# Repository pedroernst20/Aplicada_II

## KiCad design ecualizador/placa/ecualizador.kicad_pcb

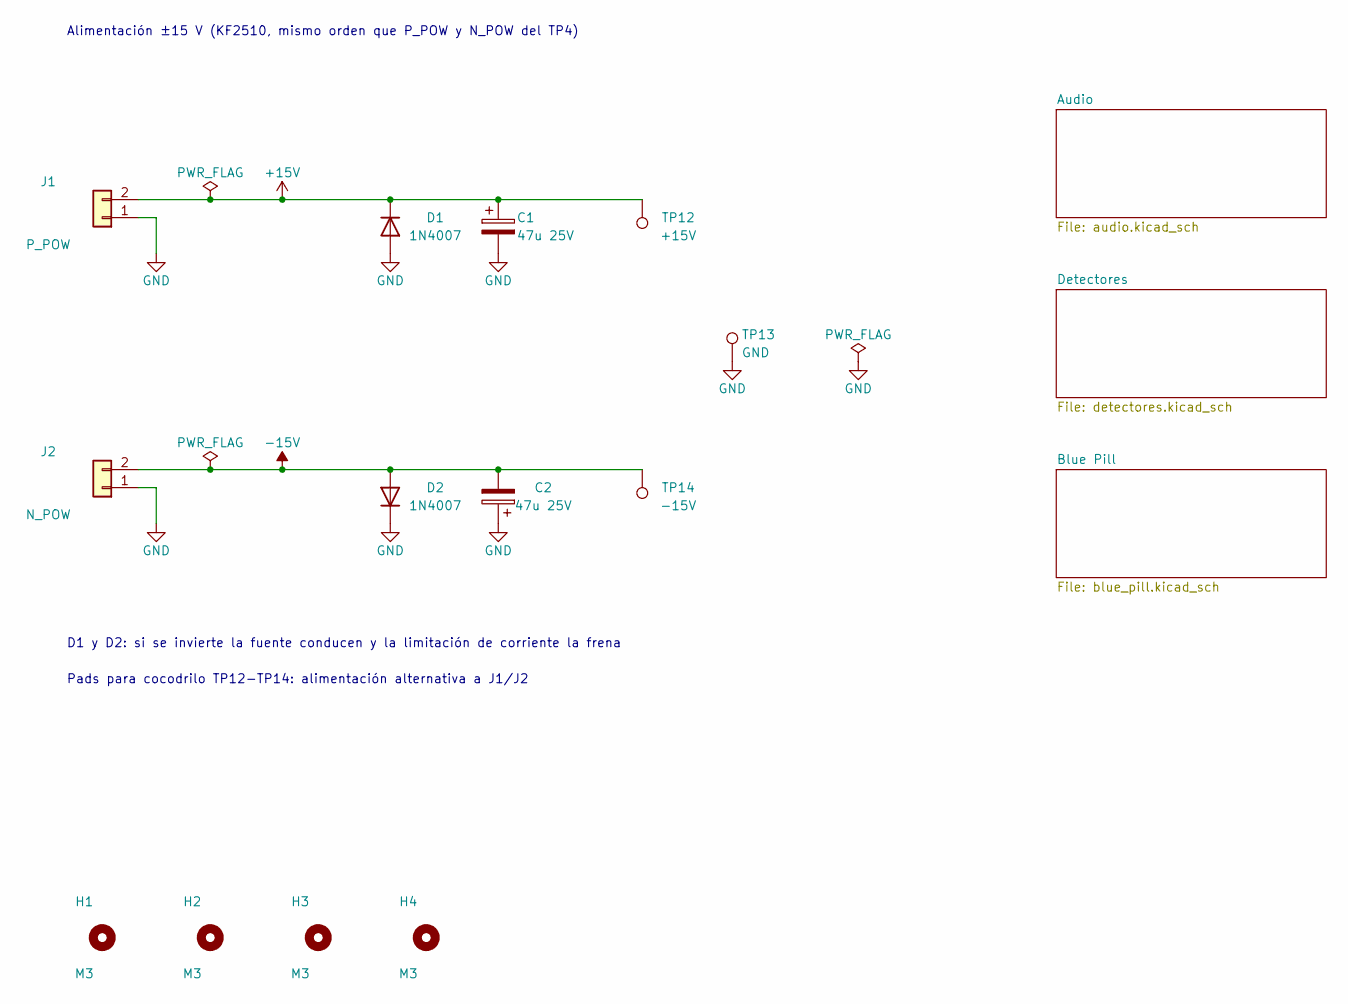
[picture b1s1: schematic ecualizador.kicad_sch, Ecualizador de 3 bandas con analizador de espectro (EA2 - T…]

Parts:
C1, C2: 47u 25V; CP_Radial_D6.3mm_P2.50mm
D1, D2: 1N4007; D_DO-41_SOD81_P10.16mm_Horizontal
H1, H2, H3, H4: M3; MountingHole_3.2mm_M3
J1: P_POW; KF2510_1x02_P2.54mm_Vertical
J2: N_POW; KF2510_1x02_P2.54mm_Vertical
TP12: +15V; Pad_Cocodrilo_6x8mm
TP13: GND; Pad_Cocodrilo_6x8mm
TP14: -15V; Pad_Cocodrilo_6x8mm

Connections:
+15V: C1.1, D1.1 (K), J1.2, TP12.1; also elsewhere on the board
-15V: C2.2, D2.2 (A), J2.2, TP14.1; also elsewhere on the board
GND: C1.2, C2.1, D1.2 (A), D2.1 (K), J1.1, J2.1, TP13.1; also elsewhere on the board

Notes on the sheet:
Alimentación ±15 V (KF2510, mismo orden que P_POW y N_POW del TP4)
D1 y D2: si se invierte la fuente conducen y la limitación de corriente la frena
Pads para cocodrilo TP12-TP14: alimentación alternativa a J1/J2

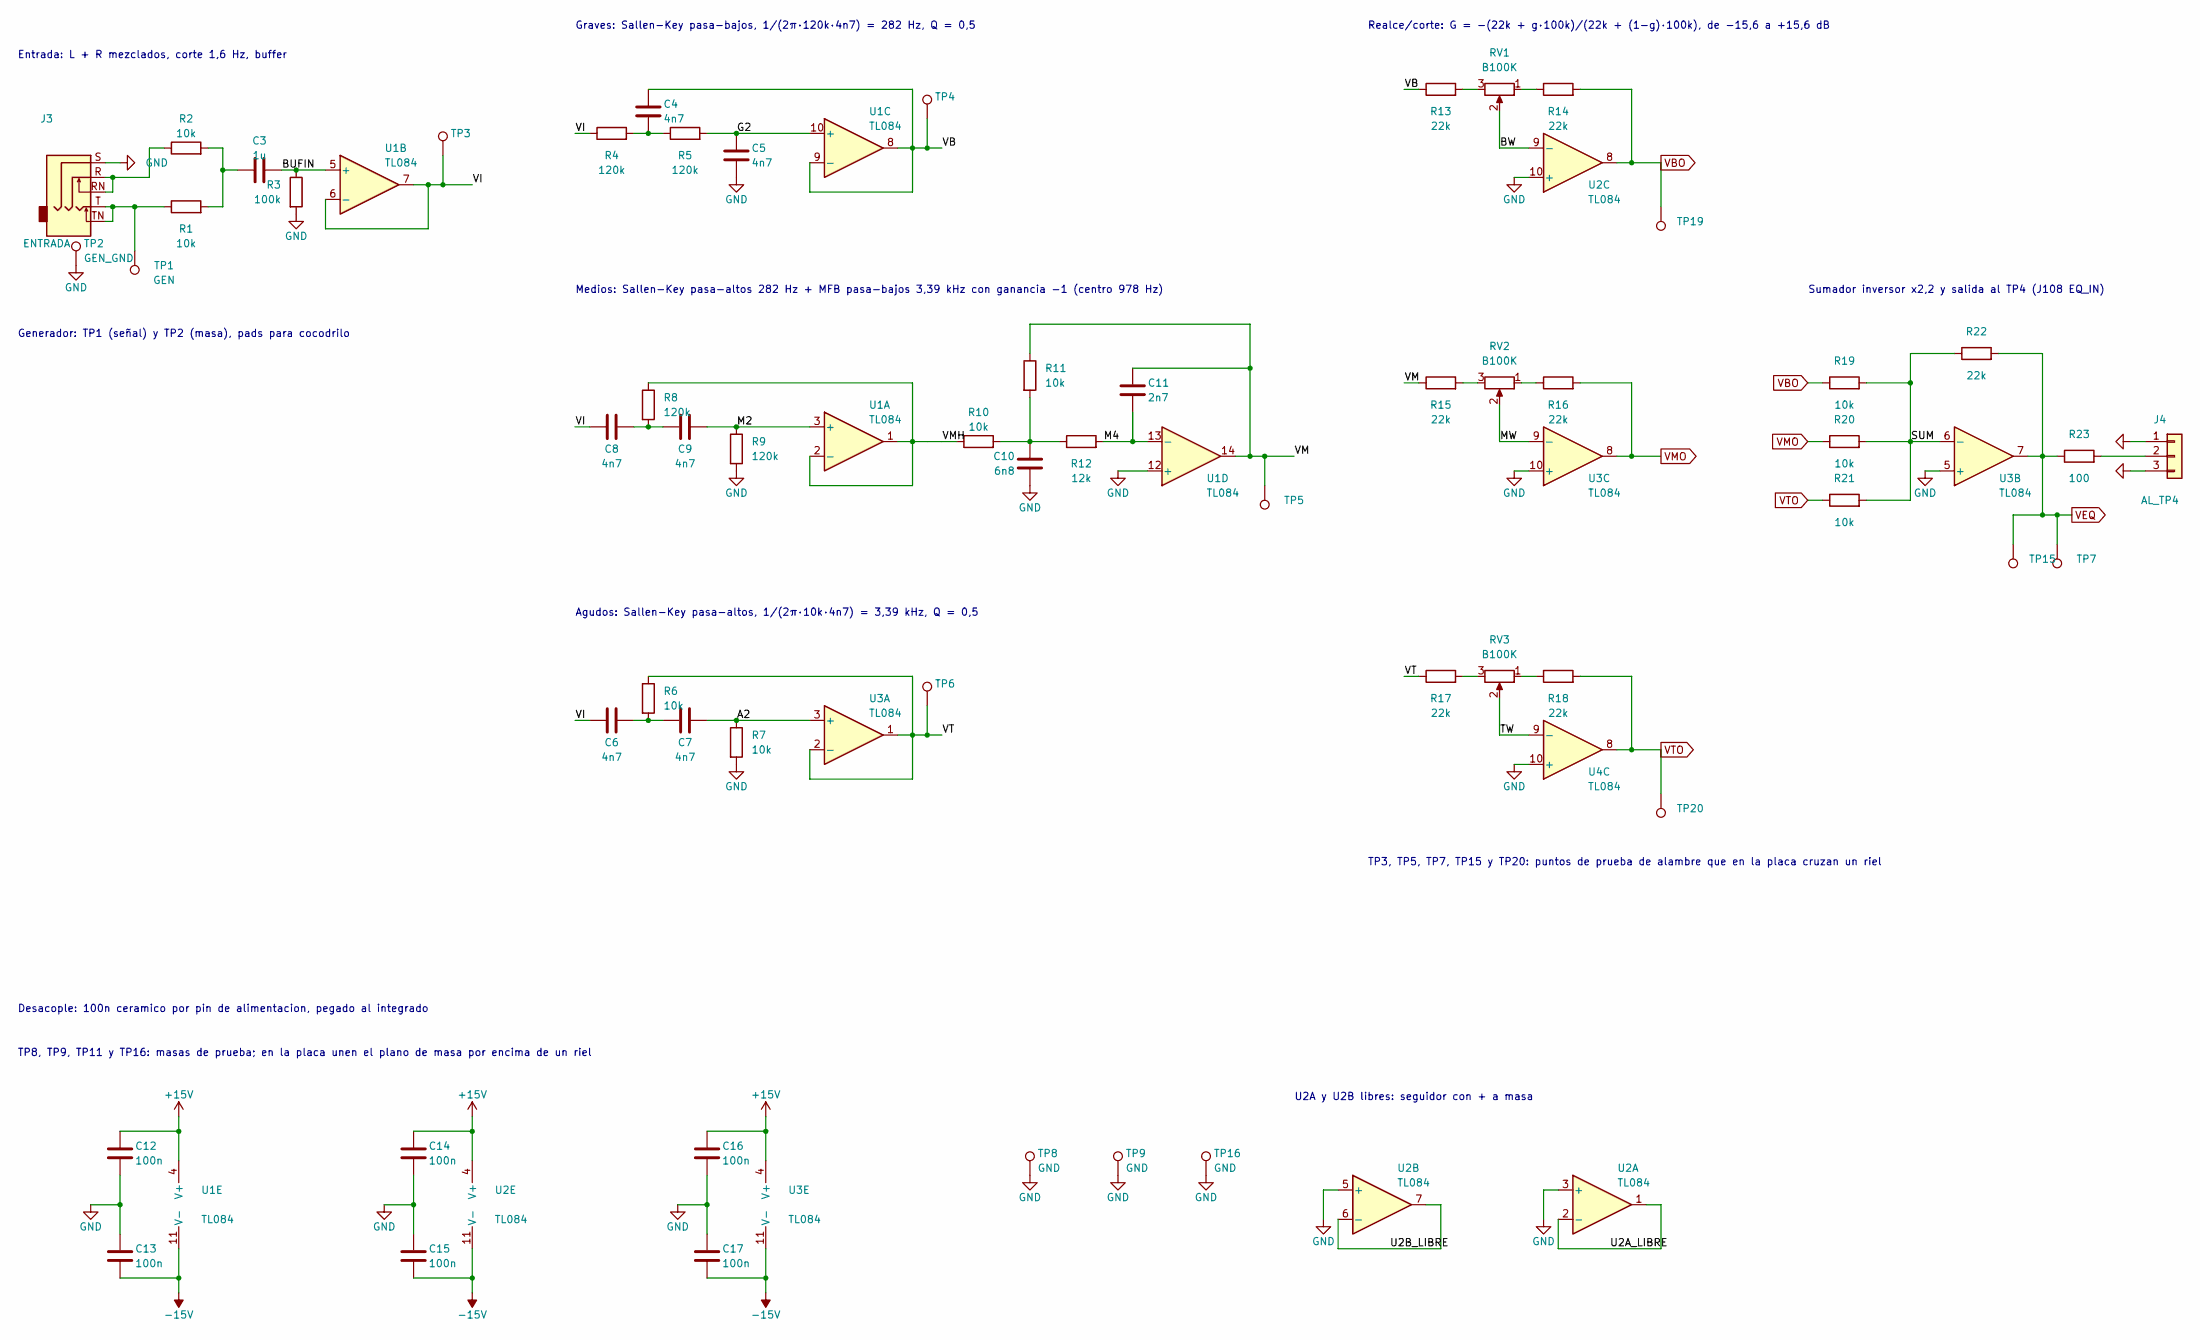
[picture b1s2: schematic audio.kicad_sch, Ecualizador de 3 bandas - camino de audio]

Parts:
C3: 1u; C_Rect_L7.2mm_W5.5mm_P5.00mm_FKS2_FKP2_MKS2_MKP2
C4, C5, C6, C7, C8, C9: 4n7; C_Rect_L7.2mm_W2.5mm_P5.00mm_FKS2_FKP2_MKS2_MKP2
C10: 6n8; C_Rect_L13.0mm_W6.0mm_P10.00mm_FKS3_FKP3_MKS4
C11: 2n7; C_Rect_L7.2mm_W2.5mm_P5.00mm_FKS2_FKP2_MKS2_MKP2
C12, C13, C14, C15, C16, C17: 100n; C_Disc_D5.0mm_W2.5mm_P5.00mm
J3: ENTRADA; Jack_3.5mm_PJ307_5pin_Horizontal
J4: AL_TP4; KF2510_1x03_P2.54mm_Vertical
R1, R2, R6, R7, R11, R20, R21: 10k; R_Axial_DIN0207_L6.3mm_D2.5mm_P10.16mm_Horizontal
R3: 100k; R_Axial_DIN0207_L6.3mm_D2.5mm_P10.16mm_Horizontal
R4, R5, R8, R9: 120k; R_Axial_DIN0207_L6.3mm_D2.5mm_P10.16mm_Horizontal
R10: 10k; R_Axial_DIN0207_L6.3mm_D2.5mm_P12.70mm_Horizontal
R12: 12k; R_Axial_DIN0207_L6.3mm_D2.5mm_P10.16mm_Horizontal
R13, R14, R15, R16, R17, R18, R22: 22k; R_Axial_DIN0207_L6.3mm_D2.5mm_P10.16mm_Horizontal
R19: 10k; R_Axial_DIN0207_L6.3mm_D2.5mm_P15.24mm_Horizontal
R23: 100; R_Axial_DIN0207_L6.3mm_D2.5mm_P12.70mm_Horizontal
RV1, RV2, RV3: B100K; Pote_16mm_Lengueta_90grados
TP1: GEN; Pad_Cocodrilo_6x8mm
TP2: GEN_GND; Pad_Cocodrilo_6x8mm
TP3, TP5, TP7, TP15, TP20: TP; TP_Puente_P7.62mm
TP4, TP6, TP19: TP; TP_Puente_P5.08mm
TP8, TP9, TP16: GND; TP_Puente_P7.62mm
U1, U2, U3, U4: TL084; DIP-14_W7.62mm_Socket_LongPads

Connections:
+15V: C12.1, C14.1, C16.1, U1.4 (V+), U2.4 (V+), U3.4 (V+); also elsewhere on the board
-15V: C13.2, C15.2, C17.2, U1.11 (V-), U2.11 (V-), U3.11 (V-); also elsewhere on the board
/Audio/A2: C7.2, R7.1, U3.3 (+)
/Audio/BUFIN: C3.2, R3.1, U1.5 (+)
/Audio/BW: RV1.2, U2.9 (-)
/Audio/G2: C5.1, R5.2, U1.10 (+)
/Audio/M2: C9.2, R9.1, U1.3 (+)
/Audio/M4: C11.2, R12.2, U1.13 (-)
/Audio/MW: RV2.2, U3.9 (-)
/Audio/SUM: R19.2, R20.2, R21.2, R22.1, U3.6 (-)
/Audio/TW: RV3.2, U4.9 (-)
/Audio/U2A_LIBRE: U2.1, U2.2 (-)
/Audio/U2B_LIBRE: U2.6 (-), U2.7
/Audio/VB: C4.1, R13.1, TP4.1, U1.8, U1.9 (-)
/Audio/VI: C6.1, C8.1, R4.1, TP3.1, U1.6 (-), U1.7
/Audio/VM: C11.1, R11.1, R15.1, TP5.1, U1.14
/Audio/VMH: R8.1, R10.1, U1.1, U1.2 (-)
/Audio/VT: R6.1, R17.1, TP6.1, U3.1, U3.2 (-)
GND: C5.2, C10.2, C12.2, C13.1, C14.2, C15.1, C16.2, C17.1, J3.S, J4.1, J4.3, R3.2, R7.2, R9.2, TP2.1, TP8.1, TP9.1, TP16.1, U1.12 (+), U2.3 (+), U2.5 (+), U2.10 (+), U3.5 (+), U3.10 (+), U4.10 (+); also elsewhere on the board
unnamed: C3.1, R1.2, R2.2
unnamed: C4.2, R4.2, R5.1
unnamed: C6.2, C7.1, R6.2
unnamed: C8.2, C9.1, R8.2
unnamed: C10.1, R10.2, R11.2, R12.1
unnamed: J3.R, J3.RN, R2.1
unnamed: J3.T, J3.TN, R1.1, TP1.1
unnamed: J4.2, R23.2
unnamed: R13.2, RV1.3
unnamed: R14.1, RV1.1
unnamed: R15.2, RV2.3
unnamed: R16.1, RV2.1
unnamed: R17.2, RV3.3
unnamed: R18.1, RV3.1
VBO: R14.2, R19.1, TP19.1, U2.8; also elsewhere on the board
VEQ: R22.2, R23.1, TP7.1, TP15.1, U3.7; also elsewhere on the board
VMO: R16.2, R20.1, U3.8; also elsewhere on the board
VTO: R18.2, R21.1, TP20.1, U4.8; also elsewhere on the board

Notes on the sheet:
Generador: TP1 (señal) y TP2 (masa), pads para cocodrilo
Entrada: L + R mezclados, corte 1,6 Hz, buffer
Graves: Sallen-Key pasa-bajos, 1/(2π·120k·4n7) = 282 Hz, Q = 0,5
Medios: Sallen-Key pasa-altos 282 Hz + MFB pasa-bajos 3,39 kHz con ganancia -1 (centro 978 Hz)
Agudos: Sallen-Key pasa-altos, 1/(2π·10k·4n7) = 3,39 kHz, Q = 0,5
Realce/corte: G = -(22k + g·100k)/(22k + (1-g)·100k), de -15,6 a +15,6 dB
TP3, TP5, TP7, TP15 y TP20: puntos de prueba de alambre que en la placa cruzan un riel
Sumador inversor x2,2 y salida al TP4 (J108 EQ_IN)
Desacople: 100n ceramico por pin de alimentacion, pegado al integrado
U2A y U2B libres: seguidor con + a masa
TP8, TP9, TP11 y TP16: masas de prueba; en la placa unen el plano de masa por encima de un riel

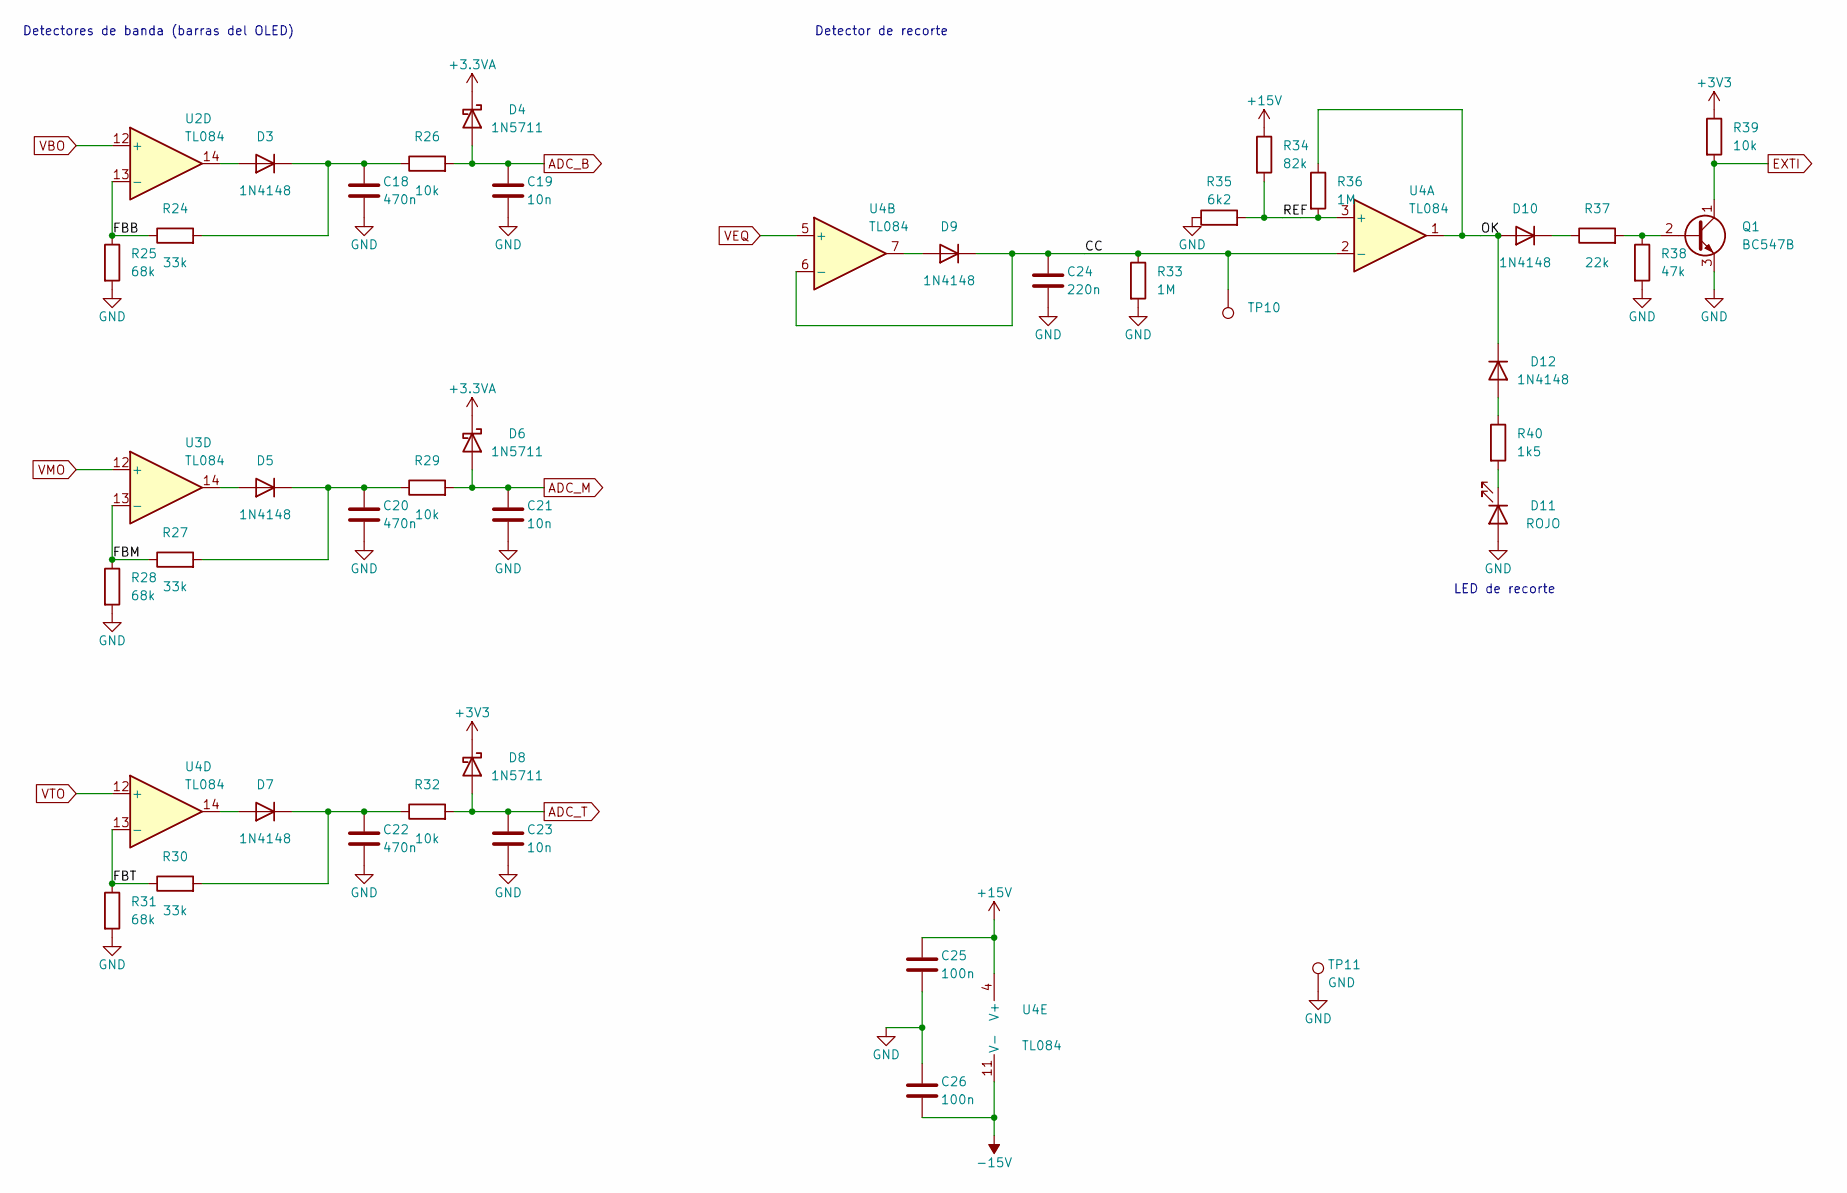
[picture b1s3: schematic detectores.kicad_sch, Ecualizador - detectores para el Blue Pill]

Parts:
C18, C20, C22: 470n; C_Rect_L13.0mm_W6.0mm_P10.00mm_FKS3_FKP3_MKS4
C19, C21, C23: 10n; C_Rect_L7.2mm_W2.5mm_P5.00mm_FKS2_FKP2_MKS2_MKP2
C24: 220n; C_Rect_L13.0mm_W6.0mm_P10.00mm_FKS3_FKP3_MKS4
C25, C26: 100n; C_Disc_D5.0mm_W2.5mm_P5.00mm
D3, D5, D7, D9, D10, D12: 1N4148; D_DO-35_SOD27_P7.62mm_Horizontal
D4, D6, D8: 1N5711; D_DO-35_SOD27_P7.62mm_Horizontal
D11: ROJO; LED_D5.0mm
Q1: BC547B; TO-92_Inline_Wide
R24, R27, R30: 33k; R_Axial_DIN0207_L6.3mm_D2.5mm_P10.16mm_Horizontal
R25, R28, R31: 68k; R_Axial_DIN0207_L6.3mm_D2.5mm_P10.16mm_Horizontal
R26, R29, R32: 10k; R_Axial_DIN0207_L6.3mm_D2.5mm_P15.24mm_Horizontal
R33, R36: 1M; R_Axial_DIN0207_L6.3mm_D2.5mm_P10.16mm_Horizontal
R34: 82k; R_Axial_DIN0207_L6.3mm_D2.5mm_P10.16mm_Horizontal
R35: 6k2; R_Axial_DIN0207_L6.3mm_D2.5mm_P10.16mm_Horizontal
R37: 22k; R_Axial_DIN0207_L6.3mm_D2.5mm_P10.16mm_Horizontal
R38: 47k; R_Axial_DIN0207_L6.3mm_D2.5mm_P10.16mm_Horizontal
R39: 10k; R_Axial_DIN0207_L6.3mm_D2.5mm_P10.16mm_Horizontal
R40: 1k5; R_Axial_DIN0207_L6.3mm_D2.5mm_P10.16mm_Horizontal
TP10: TP; TP_Puente_P5.08mm
TP11: GND; TP_Puente_P7.62mm
U2, U3, U4: TL084; DIP-14_W7.62mm_Socket_LongPads

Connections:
+3.3VA: D4.1 (K), D6.1 (K); also elsewhere on the board
+3V3: D8.1 (K), R39.1; also elsewhere on the board
+15V: C25.1, R34.1, U4.4 (V+); also elsewhere on the board
-15V: C26.2, U4.11 (V-); also elsewhere on the board
/Detectores/CC: C24.1, D9.1 (K), R33.1, TP10.1, U4.2 (-), U4.6 (-)
/Detectores/FBB: R24.1, R25.1, U2.13 (-)
/Detectores/FBM: R27.1, R28.1, U3.13 (-)
/Detectores/FBT: R30.1, R31.1, U4.13 (-)
/Detectores/OK: D10.2 (A), D12.1 (K), R36.1, U4.1
/Detectores/REF: R34.2, R35.2, R36.2, U4.3 (+)
ADC_B: C19.1, D4.2 (A), R26.2; also elsewhere on the board
ADC_M: C21.1, D6.2 (A), R29.2; also elsewhere on the board
ADC_T: C23.1, D8.2 (A), R32.2; also elsewhere on the board
EXTI: Q1.1 (C), R39.2; also elsewhere on the board
GND: C18.2, C19.2, C20.2, C21.2, C22.2, C23.2, C24.2, C25.2, C26.1, D11.2 (A), Q1.3 (E), R25.2, R28.2, R31.2, R33.2, R35.1, R38.2, TP11.1; also elsewhere on the board
unnamed: D3.2 (A), U2.14
unnamed: C18.1, D3.1 (K), R24.2, R26.1
unnamed: D5.2 (A), U3.14
unnamed: C20.1, D5.1 (K), R27.2, R29.1
unnamed: D7.2 (A), U4.14
unnamed: C22.1, D7.1 (K), R30.2, R32.1
unnamed: D9.2 (A), U4.7
unnamed: D10.1 (K), R37.1
unnamed: D11.1 (K), R40.2
unnamed: D12.2 (A), R40.1
unnamed: Q1.2 (B), R37.2, R38.1
VBO: U2.12 (+); also elsewhere on the board
VEQ: U4.5 (+); also elsewhere on the board
VMO: U3.12 (+); also elsewhere on the board
VTO: U4.12 (+); also elsewhere on the board

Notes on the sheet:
Detectores de banda (barras del OLED)
Detector de recorte
LED de recorte

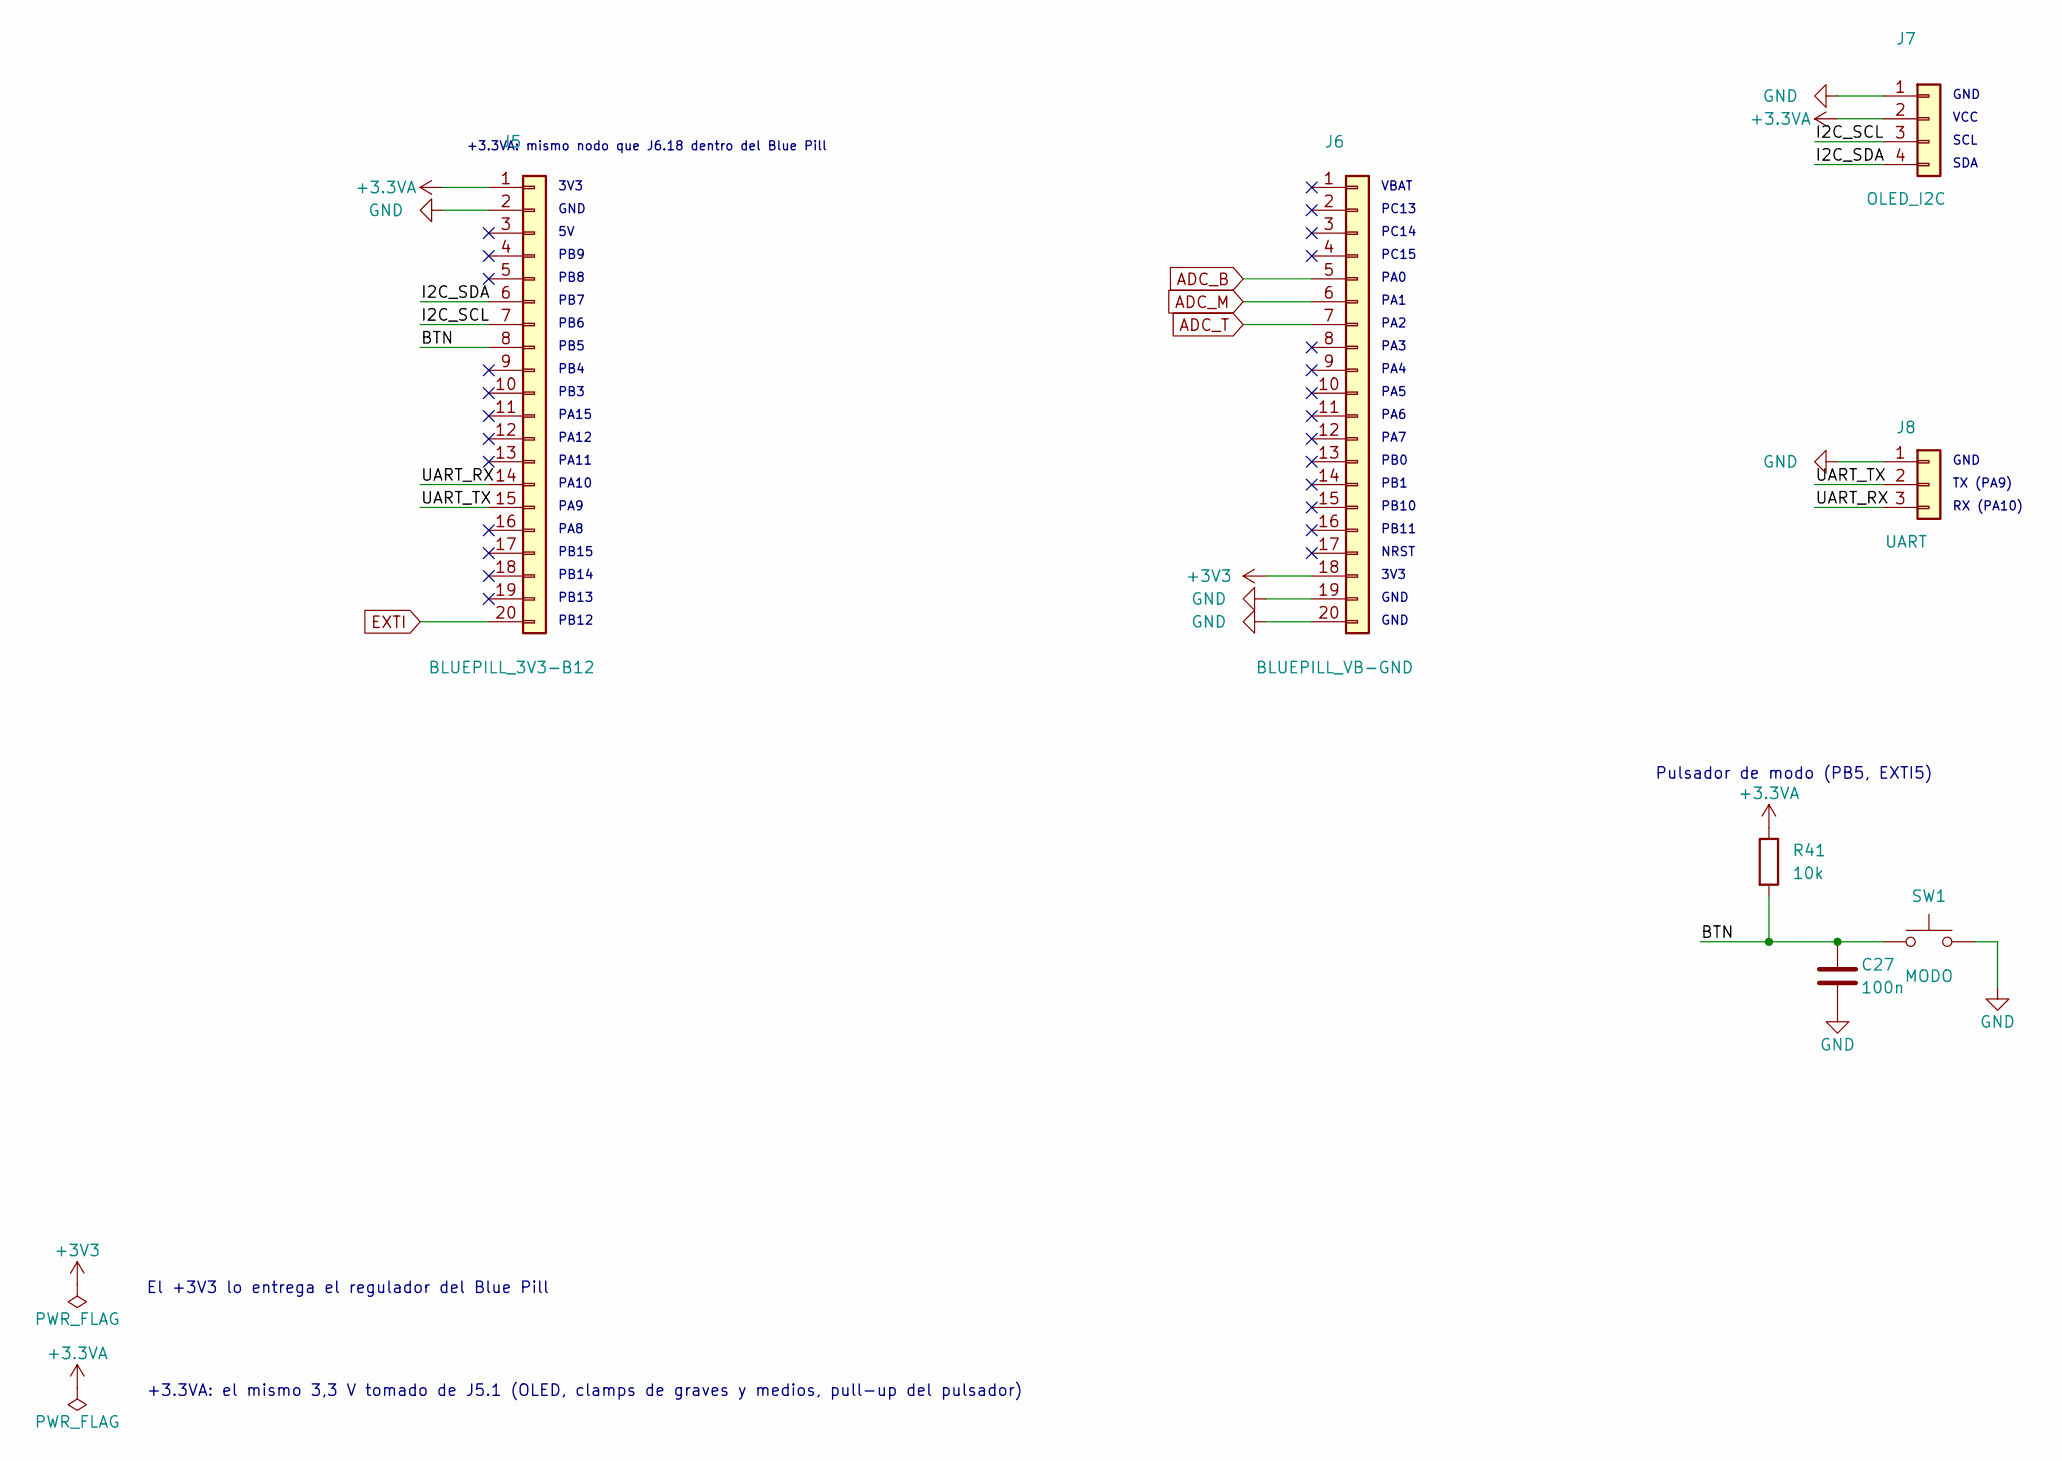
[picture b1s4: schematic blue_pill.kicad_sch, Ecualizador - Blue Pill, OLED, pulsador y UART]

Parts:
C27: 100n; C_Disc_D5.0mm_W2.5mm_P5.00mm
J5: BLUEPILL_3V3-B12; PinSocket_1x20_P2.54mm_Vertical
J6: BLUEPILL_VB-GND; PinSocket_1x20_P2.54mm_Vertical
J7: OLED_I2C; PinSocket_1x04_P2.54mm_Vertical
J8: UART; PinHeader_1x03_P2.54mm_Vertical
R41: 10k; R_Axial_DIN0207_L6.3mm_D2.5mm_P10.16mm_Horizontal
SW1: MODO; SW_PUSH_6mm

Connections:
+3.3VA: J5.1, J7.2, R41.1; also elsewhere on the board
+3V3: J6.18; also elsewhere on the board
/Blue Pill/BTN: C27.1, J5.8, R41.2, SW1.1
/Blue Pill/I2C_SCL: J5.7, J7.3
/Blue Pill/I2C_SDA: J5.6, J7.4
/Blue Pill/UART_RX: J5.14, J8.3
/Blue Pill/UART_TX: J5.15, J8.2
ADC_B: J6.5; also elsewhere on the board
ADC_M: J6.6; also elsewhere on the board
ADC_T: J6.7; also elsewhere on the board
EXTI: J5.20; also elsewhere on the board
GND: C27.2, J5.2, J6.19, J6.20, J7.1, J8.1, SW1.2; also elsewhere on the board

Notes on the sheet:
3V3
+3.3VA: mismo nodo que J6.18 dentro del Blue Pill
GND
PB9
PB8
PB7
PB6
PB5
PB4
PB3
PA15
PA12
PA11
PA10
PA9
PA8
PB15
PB14
PB13
PB12
VBAT
PC13
PC14
PC15
PA0
PA1
PA2
PA3
PA4
PA5
PA6
PA7
PB0
PB1
PB10
PB11
NRST
VCC
SCL
SDA

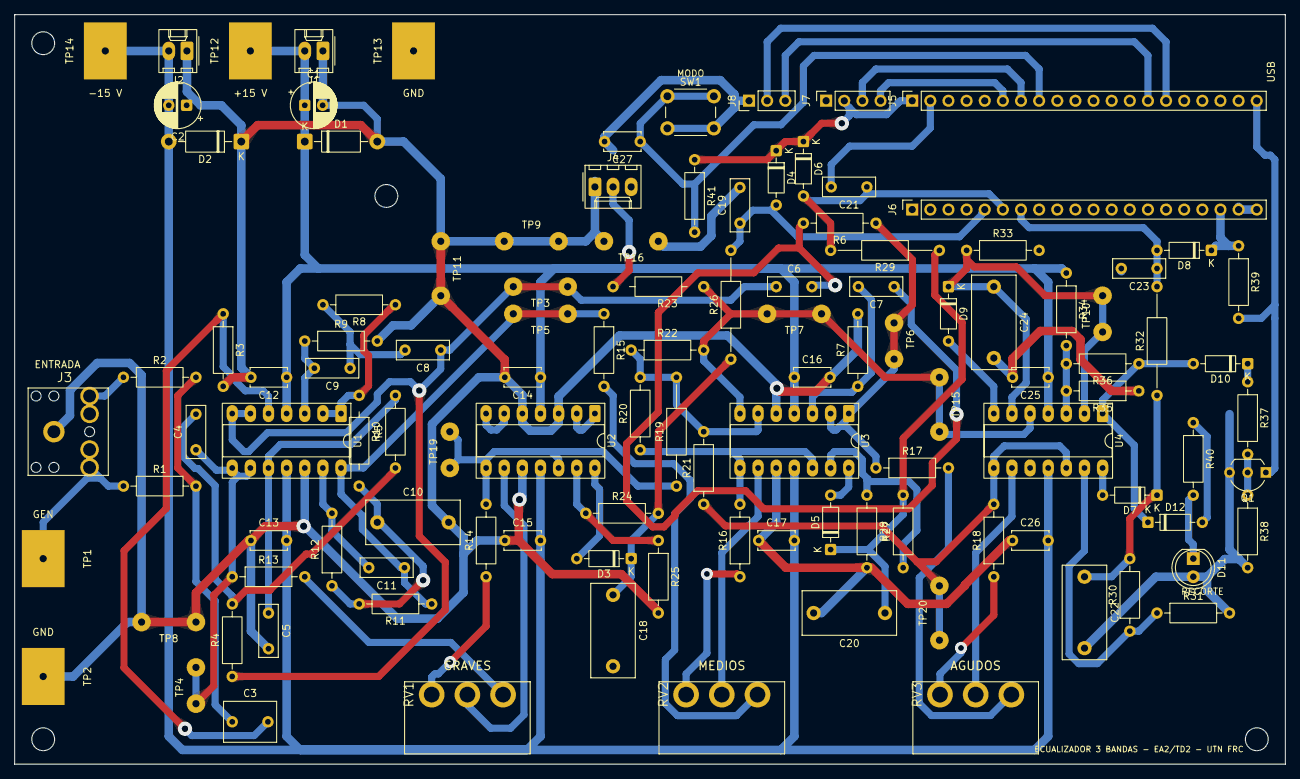
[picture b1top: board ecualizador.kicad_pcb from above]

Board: 2 copper layers, 178.0 x 105.0 mm, 119 parts (0 on the bottom side), 65 nets.

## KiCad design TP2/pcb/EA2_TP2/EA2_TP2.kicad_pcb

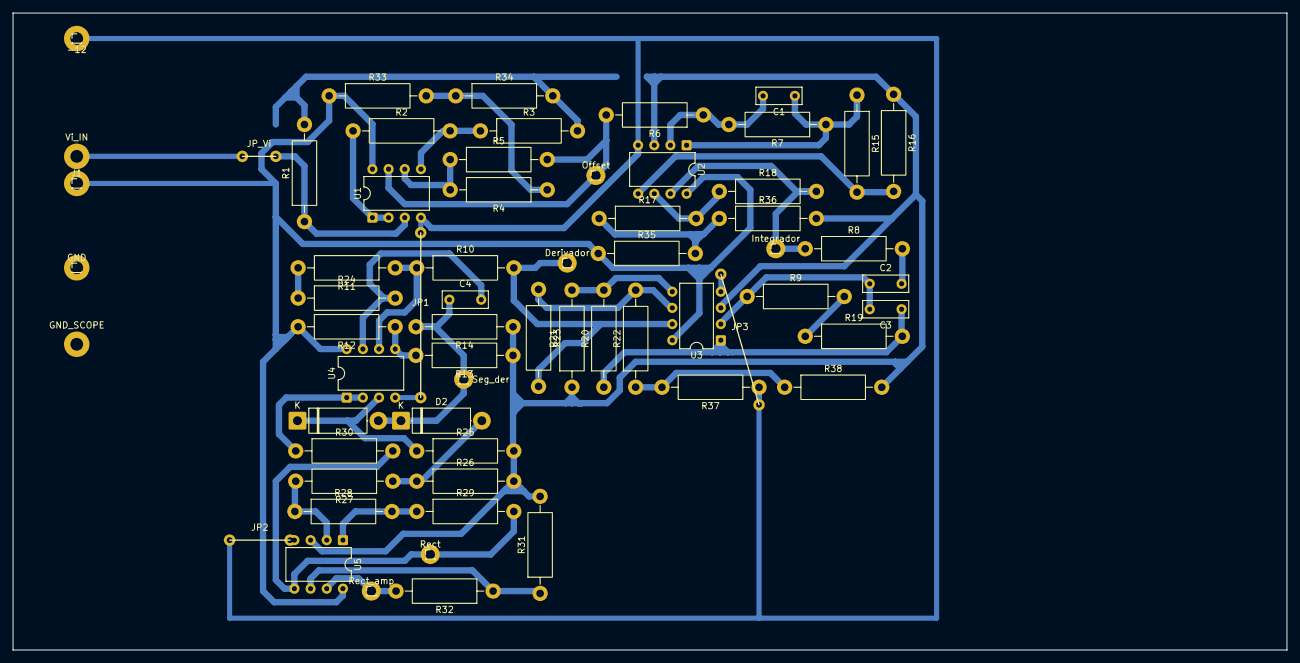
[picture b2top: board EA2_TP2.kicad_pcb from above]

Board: 2 copper layers, 200.0 x 100.0 mm, 64 parts (0 on the bottom side), 36 nets.

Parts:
-12: Conn_01x01_Pin; TestPoint_THTPad_D4.0mm_Drill2.0mm
C1, C4: 10n; C_Disc_D7.0mm_W2.5mm_P5.00mm
C2: 1n; C_Disc_D7.0mm_W2.5mm_P5.00mm
C3: 56p; C_Disc_D7.0mm_W2.5mm_P5.00mm
D1, D2: D_Schottky; D_5W_P12.70mm_Horizontal
Derivador: Conn_01x01_Pin; TestPoint_THTPad_D3.0mm_Drill1.5mm
GND: GND; TestPoint_THTPad_D4.0mm_Drill2.0mm
GND_SCOPE: GND; TestPoint_THTPad_D4.0mm_Drill2.0mm
Integrador: Integrador; TestPoint_THTPad_D3.0mm_Drill1.5mm
J1: +12; TestPoint_THTPad_D4.0mm_Drill2.0mm
JP1, JP2, JP3: Jumper; Jumper_Horizontal_RM10.16mm
JP_Vi: Jumper; Jumper_Horizontal_RM10.16mm
Offset: Offset; TestPoint_THTPad_D3.0mm_Drill1.5mm
R1: 15k; R_Axial_DIN0411_L9.9mm_D3.6mm_P15.24mm_Horizontal
R2, R3, R4, R5, R7, R15, R17, R21, R23, R26: 100k; R_Axial_DIN0411_L9.9mm_D3.6mm_P15.24mm_Horizontal
R6, R12: 10k; R_Axial_DIN0411_L9.9mm_D3.6mm_P15.24mm_Horizontal
R8: 4.7k; R_Axial_DIN0411_L9.9mm_D3.6mm_P15.24mm_Horizontal
R9, R11: 6.8k; R_Axial_DIN0411_L9.9mm_D3.6mm_P15.24mm_Horizontal
R10, R19, R24, R29, R30: 56k; R_Axial_DIN0411_L9.9mm_D3.6mm_P15.24mm_Horizontal
R13: 600; R_Axial_DIN0411_L9.9mm_D3.6mm_P15.24mm_Horizontal
R14: 470; R_Axial_DIN0411_L9.9mm_D3.6mm_P15.24mm_Horizontal
R16, R18, R32: 380k; R_Axial_DIN0411_L9.9mm_D3.6mm_P15.24mm_Horizontal
R20, R22: 200k; R_Axial_DIN0411_L9.9mm_D3.6mm_P15.24mm_Horizontal
R25: 100; R_Axial_DIN0411_L9.9mm_D3.6mm_P15.24mm_Horizontal
R27, R28: 22k; R_Axial_DIN0411_L9.9mm_D3.6mm_P15.24mm_Horizontal
R31, R34, R38: 1k; R_Axial_DIN0411_L9.9mm_D3.6mm_P15.24mm_Horizontal
R33: 7k; R_Axial_DIN0411_L9.9mm_D3.6mm_P15.24mm_Horizontal
R35: 27k; R_Axial_DIN0411_L9.9mm_D3.6mm_P15.24mm_Horizontal
R36: 5.6k; R_Axial_DIN0411_L9.9mm_D3.6mm_P15.24mm_Horizontal
R37: 2.8k; R_Axial_DIN0411_L9.9mm_D3.6mm_P15.24mm_Horizontal
Rect: Conn_01x01_Pin; TestPoint_THTPad_D3.0mm_Drill1.5mm
Rect_amp: Conn_01x01_Pin; TestPoint_THTPad_D3.0mm_Drill1.5mm
Seg_der: Conn_01x01_Pin; TestPoint_THTPad_D3.0mm_Drill1.5mm
U1, U2, U3, U4, U5: TL082; DIP-8_W7.62mm_Socket
Vi_IN: Vi; TestPoint_THTPad_D4.0mm_Drill2.0mm

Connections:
/+12: J1.1 (Pin_1_1), R12.2, R33.1, R35.1, U1.8 (V+), U2.8 (V+), U3.8 (V+), U4.8 (V+), U5.8 (V+)
/-12: -12.1 (Pin_1_1), JP1.1, JP2.1, JP3.1, R37.1, U1.4 (V-), U2.4 (V-), U3.4 (V-), U4.4 (V-), U5.4 (V-)
/Adap_Zi: R2.1, U1.1, U1.2 (-)
/Derivador: Derivador.1 (Pin_1_1), R10.2, R23.2, U3.7
/Integrador: Integrador.1 (Pin_1_1), R8.1, R18.2, U2.7
/Offset: Offset.1 (Pin_1_1), R5.2, R6.2, U1.7
/Pre_der: C3.1, R19.2, R20.1, U3.1
/Pre_int: C1.1, R7.1, R15.1, U2.1
/Rect: R29.2, R30.2, Rect.1 (Pin_1_1), U5.5 (+)
/Rect_ampl: R32.2, Rect_amp.1 (Pin_1_1), U5.7
/Seg_der: C4.1, D1.2 (A), D2.1 (K), R14.2, Seg_der.1 (Pin_1_1)
/Vi: JP_Vi.1, R1.1, U1.3 (+), Vi_IN.1
/Vref_1: R4.1, R33.2, R34.1
/Vref_2: R17.1, R35.2, R36.1
/Vref_3: R22.1, R37.2, R38.1
GND: GND.1 (Pin_1_1), GND_SCOPE.1, R1.2, R3.2, R13.1, R14.1, R16.1, R21.1, R25.2, R26.2, R31.2, R34.2, R36.2, R38.2, U2.3 (+), U3.3 (+), U5.3 (+)
unnamed: C2.2, R8.2
unnamed: C4.2, R24.2, U4.7
unnamed: D1.1 (K), R25.1, U4.3 (+)
unnamed: D2.2 (A), R26.1, R27.1
unnamed: R11.2, R24.1
unnamed: R9.2, R19.1
unnamed: R28.2, R29.1, U5.1
unnamed: R2.2, R3.1, U1.5 (+)
unnamed: R4.2, R5.1, U1.6 (-)
unnamed: C1.2, R6.1, R7.2, U2.2 (-)
unnamed: R15.2, R16.2, U2.5 (+)
unnamed: R17.2, R18.1, U2.6 (-)
unnamed: C2.1, C3.2, R9.1, U3.2 (-)
unnamed: R20.2, R21.2, U3.5 (+)
unnamed: R22.2, R23.1, U3.6 (-)
unnamed: R30.1, U4.1, U4.2 (-)
unnamed: R12.1, R13.2, U4.5 (+)
unnamed: R10.1, R11.1, U4.6 (-)
unnamed: R27.2, R28.1, U5.2 (-)
unnamed: R31.1, R32.1, U5.6 (-)

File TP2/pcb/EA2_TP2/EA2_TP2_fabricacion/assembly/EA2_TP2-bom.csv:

"Designator","Val","Package","Quantity","DNP"
"C1","10n","Capacitor_THT:C_Disc_D7.0mm_W2.5mm_P5.00mm","1",""
"C2","1n","Capacitor_THT:C_Disc_D7.0mm_W2.5mm_P5.00mm","1",""
"C3","56p","Capacitor_THT:C_Disc_D7.0mm_W2.5mm_P5.00mm","1",""
"C4","10n","Capacitor_THT:C_Disc_D7.0mm_W2.5mm_P5.00mm","1",""
"D1","D_Schottky","Diode_THT:D_5W_P12.70mm_Horizontal","1",""
"D2","D_Schottky","Diode_THT:D_5W_P12.70mm_Horizontal","1",""
"J1","Conn_01x01_Pin","Connector_PinHeader_1.00mm:PinHeader_1x01_P1.00mm_Vertical","1",""
"J2","Conn_01x01_Pin","Connector_PinHeader_1.00mm:PinHeader_1x01_P1.00mm_Vertical","1",""
"J3","Conn_01x01_Pin","Connector_PinHeader_1.00mm:PinHeader_1x01_P1.00mm_Vertical","1",""
"J4","Conn_01x01_Pin","Connector_PinHeader_1.00mm:PinHeader_1x01_P1.00mm_Vertical","1",""
"J5","Conn_01x01_Pin","Connector_PinHeader_1.00mm:PinHeader_1x01_P1.00mm_Vertical","1",""
"J6","Conn_01x01_Pin","Connector_PinHeader_1.00mm:PinHeader_1x01_P1.00mm_Vertical","1",""
"J7","Conn_01x01_Pin","Connector_PinHeader_1.00mm:PinHeader_1x01_P1.00mm_Vertical","1",""
"J8","Conn_01x01_Pin","Connector_PinHeader_1.00mm:PinHeader_1x01_P1.00mm_Vertical","1",""
"J9","Conn_01x01_Pin","Connector_PinHeader_1.00mm:PinHeader_1x01_P1.00mm_Vertical","1",""
"J10","Conn_01x01_Pin","Connector_PinHeader_1.00mm:PinHeader_1x01_P1.00mm_Vertical","1",""
"R1","15k","Resistor_THT:R_Axial_DIN0411_L9.9mm_D3.6mm_P15.24mm_Horizontal","1",""
"R2","100k","Resistor_THT:R_Axial_DIN0411_L9.9mm_D3.6mm_P15.24mm_Horizontal","1",""
"R3","100k","Resistor_THT:R_Axial_DIN0411_L9.9mm_D3.6mm_P15.24mm_Horizontal","1",""
"R4","100k","Resistor_THT:R_Axial_DIN0411_L9.9mm_D3.6mm_P15.24mm_Horizontal","1",""
"R5","100k","Resistor_THT:R_Axial_DIN0411_L9.9mm_D3.6mm_P15.24mm_Horizontal","1",""
"R6","10k","Resistor_THT:R_Axial_DIN0411_L9.9mm_D3.6mm_P15.24mm_Horizontal","1",""
"R7","100k","Resistor_THT:R_Axial_DIN0411_L9.9mm_D3.6mm_P15.24mm_Horizontal","1",""
"R8","4.7k","Resistor_THT:R_Axial_DIN0411_L9.9mm_D3.6mm_P15.24mm_Horizontal","1",""
"R9","6.8k","Resistor_THT:R_Axial_DIN0411_L9.9mm_D3.6mm_P15.24mm_Horizontal","1",""
"R10","56k","Resistor_THT:R_Axial_DIN0411_L9.9mm_D3.6mm_P15.24mm_Horizontal","1",""
"R11","6.8k","Resistor_THT:R_Axial_DIN0411_L9.9mm_D3.6mm_P15.24mm_Horizontal","1",""
"R12","10k","Resistor_THT:R_Axial_DIN0411_L9.9mm_D3.6mm_P15.24mm_Horizontal","1",""
"R13","600","Resistor_THT:R_Axial_DIN0411_L9.9mm_D3.6mm_P15.24mm_Horizontal","1",""
"R14","470","Resistor_THT:R_Axial_DIN0411_L9.9mm_D3.6mm_P15.24mm_Horizontal","1",""
"R15","100k","Resistor_THT:R_Axial_DIN0411_L9.9mm_D3.6mm_P15.24mm_Horizontal","1",""
"R16","380k","Resistor_THT:R_Axial_DIN0411_L9.9mm_D3.6mm_P15.24mm_Horizontal","1",""
"R17","100k","Resistor_THT:R_Axial_DIN0411_L9.9mm_D3.6mm_P15.24mm_Horizontal","1",""
"R18","380k","Resistor_THT:R_Axial_DIN0411_L9.9mm_D3.6mm_P15.24mm_Horizontal","1",""
"R19","56k","Resistor_THT:R_Axial_DIN0411_L9.9mm_D3.6mm_P15.24mm_Horizontal","1",""
"R20","200k","Resistor_THT:R_Axial_DIN0411_L9.9mm_D3.6mm_P15.24mm_Horizontal","1",""
"R21","100k","Resistor_THT:R_Axial_DIN0411_L9.9mm_D3.6mm_P15.24mm_Horizontal","1",""
"R22","200k","Resistor_THT:R_Axial_DIN0411_L9.9mm_D3.6mm_P15.24mm_Horizontal","1",""
"R23","100k","Resistor_THT:R_Axial_DIN0411_L9.9mm_D3.6mm_P15.24mm_Horizontal","1",""
"R24","56k","Resistor_THT:R_Axial_DIN0411_L9.9mm_D3.6mm_P15.24mm_Horizontal","1",""
"R25","100","Resistor_THT:R_Axial_DIN0411_L9.9mm_D3.6mm_P15.24mm_Horizontal","1",""
"R26","100k","Resistor_THT:R_Axial_DIN0411_L9.9mm_D3.6mm_P15.24mm_Horizontal","1",""
"R27","22k","Resistor_THT:R_Axial_DIN0411_L9.9mm_D3.6mm_P15.24mm_Horizontal","1",""
"R28","22k","Resistor_THT:R_Axial_DIN0411_L9.9mm_D3.6mm_P15.24mm_Horizontal","1",""
"R29","56k","Resistor_THT:R_Axial_DIN0411_L9.9mm_D3.6mm_P15.24mm_Horizontal","1",""
"R30","56k","Resistor_THT:R_Axial_DIN0411_L9.9mm_D3.6mm_P15.24mm_Horizontal","1",""
"R31","1k","Resistor_THT:R_Axial_DIN0411_L9.9mm_D3.6mm_P15.24mm_Horizontal","1",""
"R32","380k","Resistor_THT:R_Axial_DIN0411_L9.9mm_D3.6mm_P15.24mm_Horizontal","1",""
"R33","7k","Resistor_THT:R_Axial_DIN0411_L9.9mm_D3.6mm_P15.24mm_Horizontal","1",""
"R34","1k","Resistor_THT:R_Axial_DIN0411_L9.9mm_D3.6mm_P15.24mm_Horizontal","1",""
"R35","27k","Resistor_THT:R_Axial_DIN0411_L9.9mm_D3.6mm_P15.24mm_Horizontal","1",""
"R36","5.6k","Resistor_THT:R_Axial_DIN0411_L9.9mm_D3.6mm_P15.24mm_Horizontal","1",""
"R37","2.8k","Resistor_THT:R_Axial_DIN0411_L9.9mm_D3.6mm_P15.24mm_Horizontal","1",""
"R38","1k","Resistor_THT:R_Axial_DIN0411_L9.9mm_D3.6mm_P15.24mm_Horizontal","1",""
"U1","TL082","Package_DIP:DIP-8_W7.62mm","1",""
"U2","TL082","Package_DIP:DIP-8_W7.62mm","1",""
"U3","TL082","Package_DIP:DIP-8_W7.62mm","1",""
"U4","TL082","Package_DIP:DIP-8_W7.62mm","1",""
"U5","TL082","Package_DIP:DIP-8_W7.62mm","1",""

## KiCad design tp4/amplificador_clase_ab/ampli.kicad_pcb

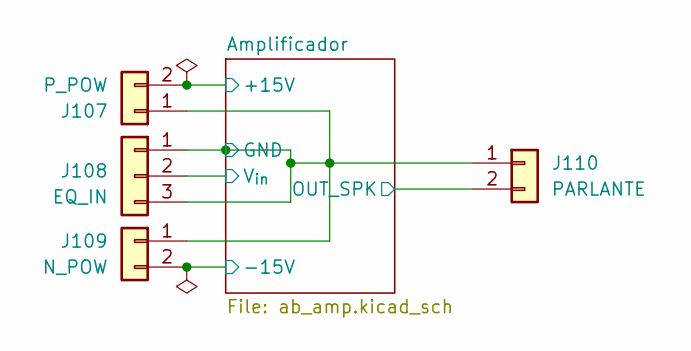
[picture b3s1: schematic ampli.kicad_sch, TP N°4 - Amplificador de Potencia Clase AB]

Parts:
J107: P_POW; KF2510_1x02_P2.54mm_Vertical
J108: EQ_IN; KF2510_1x03_P2.54mm_Vertical
J109: N_POW; KF2510_1x02_P2.54mm_Vertical
J110: PARLANTE; TerminalBlock_Phoenix_MKDS-1,5-2-5.08_1x02_P5.08mm_Horizont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

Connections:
/Amplificador/+15V: J107.2; also elsewhere on the board
/Amplificador/-15V: J109.2; also elsewhere on the board
/Amplificador/GND: J107.1, J108.1, J108.3, J109.1, J110.1; also elsewhere on the board
/Amplificador/OUT_SPK: J110.2; also elsewhere on the board
/Amplificador/V_{in}: J108.2; also elsewhere on the board
